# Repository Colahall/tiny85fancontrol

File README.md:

# Tiny85FanControl

A temperature-controlled fan system powered by an [ATtiny85](https://www.microchip.com/en-us/product/attiny85) and a [DS18B20](https://www.analog.com/media/en/technical-documentation/data-sheets/ds18b20.pdf) temperature sensor.

> ⚠️ This project is a **work in progress** and may not yet be suitable for all use cases.

## Hardware Requirements

You'll need the following components:

- [ATtiny85](https://www.microchip.com/en-us/product/attiny85) microcontroller
- [USBtinyISP](https://www.flashtree.com/products/11802) (or compatible ISP programmer)
- [DS18B20](https://www.analog.com/media/en/technical-documentation/data-sheets/ds18b20.pdf) 1-Wire temperature sensor
- Passive components (resistors, capacitors, etc.)

Refer to the [Bill of Materials (BOM)](schematic/info/tiny85fancontrol-bom.csv) for part numbers and quantities.

## Software Setup

### Ubuntu 24.04 LTS

```bash
sudo apt-get install build-essential avrdude gcc-avr binutils-avr avr-libc git
````

### Fedora 42

```bash
sudo dnf install avrdude avr-gcc avr-libc git
```

### macOS (via [Homebrew](https://brew.sh/))

```bash
brew tap osx-cross/avr
brew install avr-gcc avrdude git
```

### Windows

Use [WSL](https://docs.microsoft.com/en-us/windows/wsl/install) and follow the **Ubuntu** instructions inside your Linux environment.

## Building and uploading

To build this project, run `make` in the root directory of the project.

```bash
cd /path/to/project/

make        # Builds the binary
make fuse   # Fuses the chip with the configuration
make flash  # Uploads to the ATtiny85 via USBtinyISP
```

## Project Status

This project is working well for my needs, but there are still some things that could be improved.

Feel free to open an issue or submit a pull request if you have any ideas for improvements!

## Contributing

Pull requests and issues are welcome! If you’ve got a feature idea or fix, feel free to:

1. Fork this repo
2. Create a feature branch
3. Push and open a pull request

Please follow the existing code style and structure where possible.

## License

This project is licensed under the [MIT License](LICENSE).

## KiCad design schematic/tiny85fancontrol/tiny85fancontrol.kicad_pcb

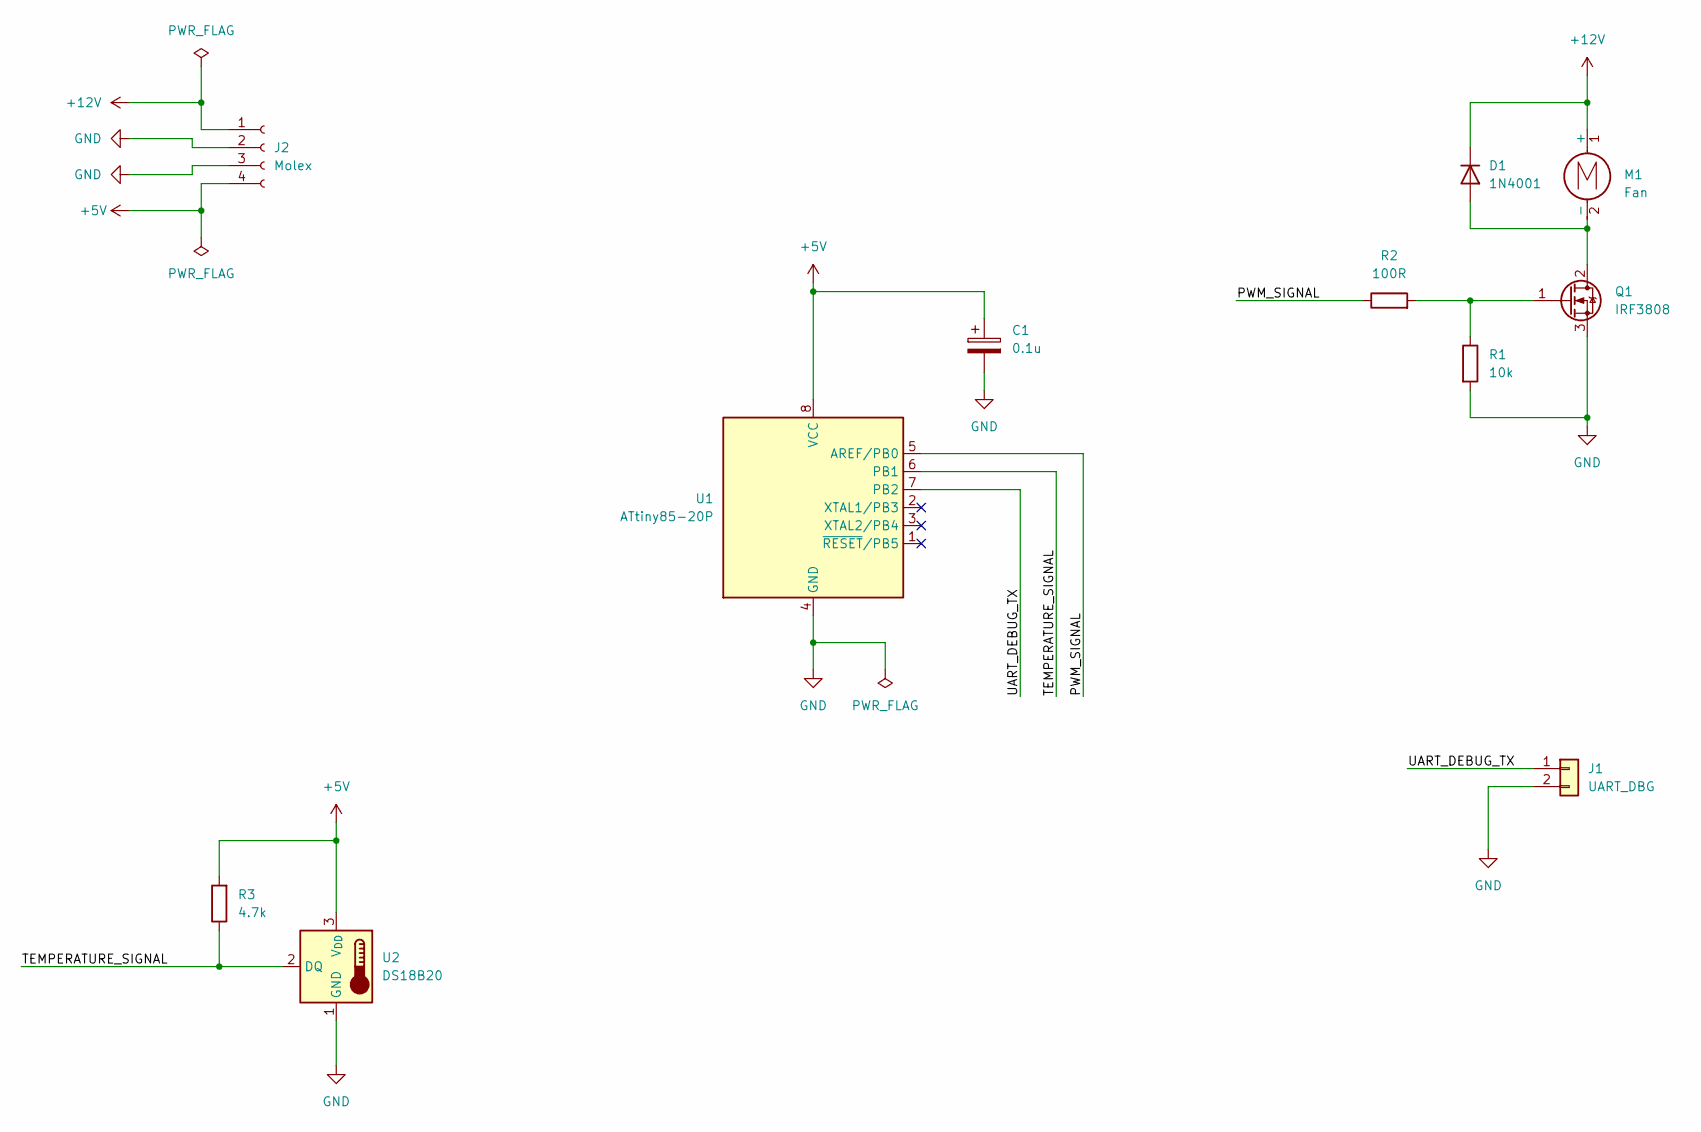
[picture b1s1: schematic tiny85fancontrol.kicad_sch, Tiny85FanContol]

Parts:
C1: 0.1u; CP_Radial_D4.0mm_P2.00mm
D1: 1N4001; D_DO-41_SOD81_P10.16mm_Horizontal
J1: UART_DBG; PinHeader_1x02_P2.54mm_Vertical
J2: Molex; Molex_KK-254_AE-6410-04A_1x04_P2.54mm_Vertical
M1: Fan; PinHeader_1x02_P2.54mm_Vertical
Q1: IRF3808; TO-220-3_Vertical
R1: 10k; R_Axial_DIN0204_L3.6mm_D1.6mm_P1.90mm_Vertical
R2: 100R; R_Axial_DIN0204_L3.6mm_D1.6mm_P1.90mm_Vertical
R3: 4.7k; R_Axial_DIN0204_L3.6mm_D1.6mm_P1.90mm_Vertical
U1: ATtiny85-20P; DIP-8_W7.62mm
U2: DS18B20; TO-92_Inline

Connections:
+5V: C1.1, J2.4, R3.2, U1.8 (VCC), U2.3 (V_{DD})
+12V: D1.1 (K), J2.1, M1.1 (+)
/PWM_SIGNAL: R2.1, U1.5 (AREF/PB0)
/TEMPERATURE_SIGNAL: R3.1, U1.6 (PB1), U2.2 (DQ)
/UART_DEBUG_TX: J1.1, U1.7 (PB2)
GND: C1.2, J1.2, J2.2, J2.3, Q1.3 (S), R1.2, U1.4 (GND), U2.1 (GND)
unnamed: D1.2 (A), M1.2 (-), Q1.2 (D)
unnamed: Q1.1 (G), R1.1, R2.2

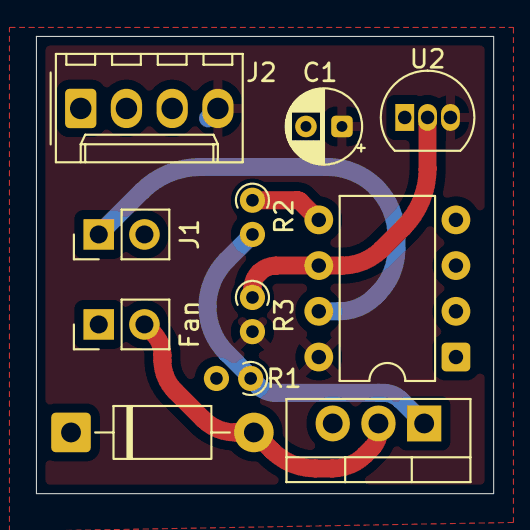
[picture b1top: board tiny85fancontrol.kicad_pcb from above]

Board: 2 copper layers, 25.4 x 25.4 mm, 11 parts (0 on the bottom side), 8 nets.

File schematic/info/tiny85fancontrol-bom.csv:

"Reference","Qty","Value","DNP","Exclude from BOM","Exclude from Board","Footprint","Datasheet"
"C1","1","0.1u","","","","Capacitor_THT:CP_Radial_D4.0mm_P2.00mm","~"
"D1","1","1N4001","","","","Diode_THT:D_DO-41_SOD81_P10.16mm_Horizontal","http://www.vishay.com/docs/88503/1n4001.pdf"
"J1","1","UART_DBG","","","","Connector_PinHeader_2.54mm:PinHeader_1x02_P2.54mm_Vertical","~"
"J2","1","Molex","","","","Connector_Molex:Molex_KK-254_AE-6410-04A_1x04_P2.54mm_Vertical","~"
"M1","1","Fan","","","","Connector_PinHeader_2.54mm:PinHeader_1x02_P2.54mm_Vertical","~"
"Q1","1","IRF3808","","","","Package_TO_SOT_THT:TO-220-3_Vertical","http://www.irf.com/product-info/datasheets/data/irf3205.pdf"
"R1","1","10k","","","","Resistor_THT:R_Axial_DIN0204_L3.6mm_D1.6mm_P1.90mm_Vertical","~"
"R2","1","100R","","","","Resistor_THT:R_Axial_DIN0204_L3.6mm_D1.6mm_P1.90mm_Vertical","~"
"R3","1","4.7k","","","","Resistor_THT:R_Axial_DIN0204_L3.6mm_D1.6mm_P1.90mm_Vertical","~"
"U1","1","ATtiny85-20P","","","","Package_DIP:DIP-8_W7.62mm","http://ww1.microchip.com/downloads/en/DeviceDoc/atmel-2586-a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"
"U2","1","DS18B20","","","","Package_TO_SOT_THT:TO-92_Inline","http://datasheets.maximintegrated.com/en/ds/DS18B20.pdf"

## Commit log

2025-07-08 Change license to MIT
2025-07-10 1-Wire and Temp Sensor Complete
2025-07-10 Add PWM control and fan curve functionality
    - Implement PWM driver with initialization and duty cycle control.
    - Introduce fan curve logic for temperature-based PWM adjustments.
    - Update main application to utilize new PWM and fan curve features.
    - Include necessary header files and adjust UART definitions.
2025-07-13 Adjust fan curve for 12V
2025-07-13 Increase initial PWM duty cycle duration for fan ramp-up
2025-07-14 Add schematic and PCB
2025-07-14 Fix: Temperature sensor connected backwards
    Thanks to amdj at #kicad for spotting this issue
2025-07-15 Update README
    Update project description, hardware requirements, and software setup instructions
    Add BOM and PCB image
2025-07-15 Refactor Makefile
2025-07-15 Add instruction to fuse the chip in README
2025-07-15 Fix: Update USBtinyISP link in README
2025-08-07 Update Schematic and PCB According to Reviews
    Placed temperature sensor away from MOSFET.
    Fixed PIN assignments according to software.

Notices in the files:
schematic/tiny85fancontrol/tiny85fancontrol.kicad_sch:
Copyright (C) 2025 Colahall, LLC. All rights reserved.
